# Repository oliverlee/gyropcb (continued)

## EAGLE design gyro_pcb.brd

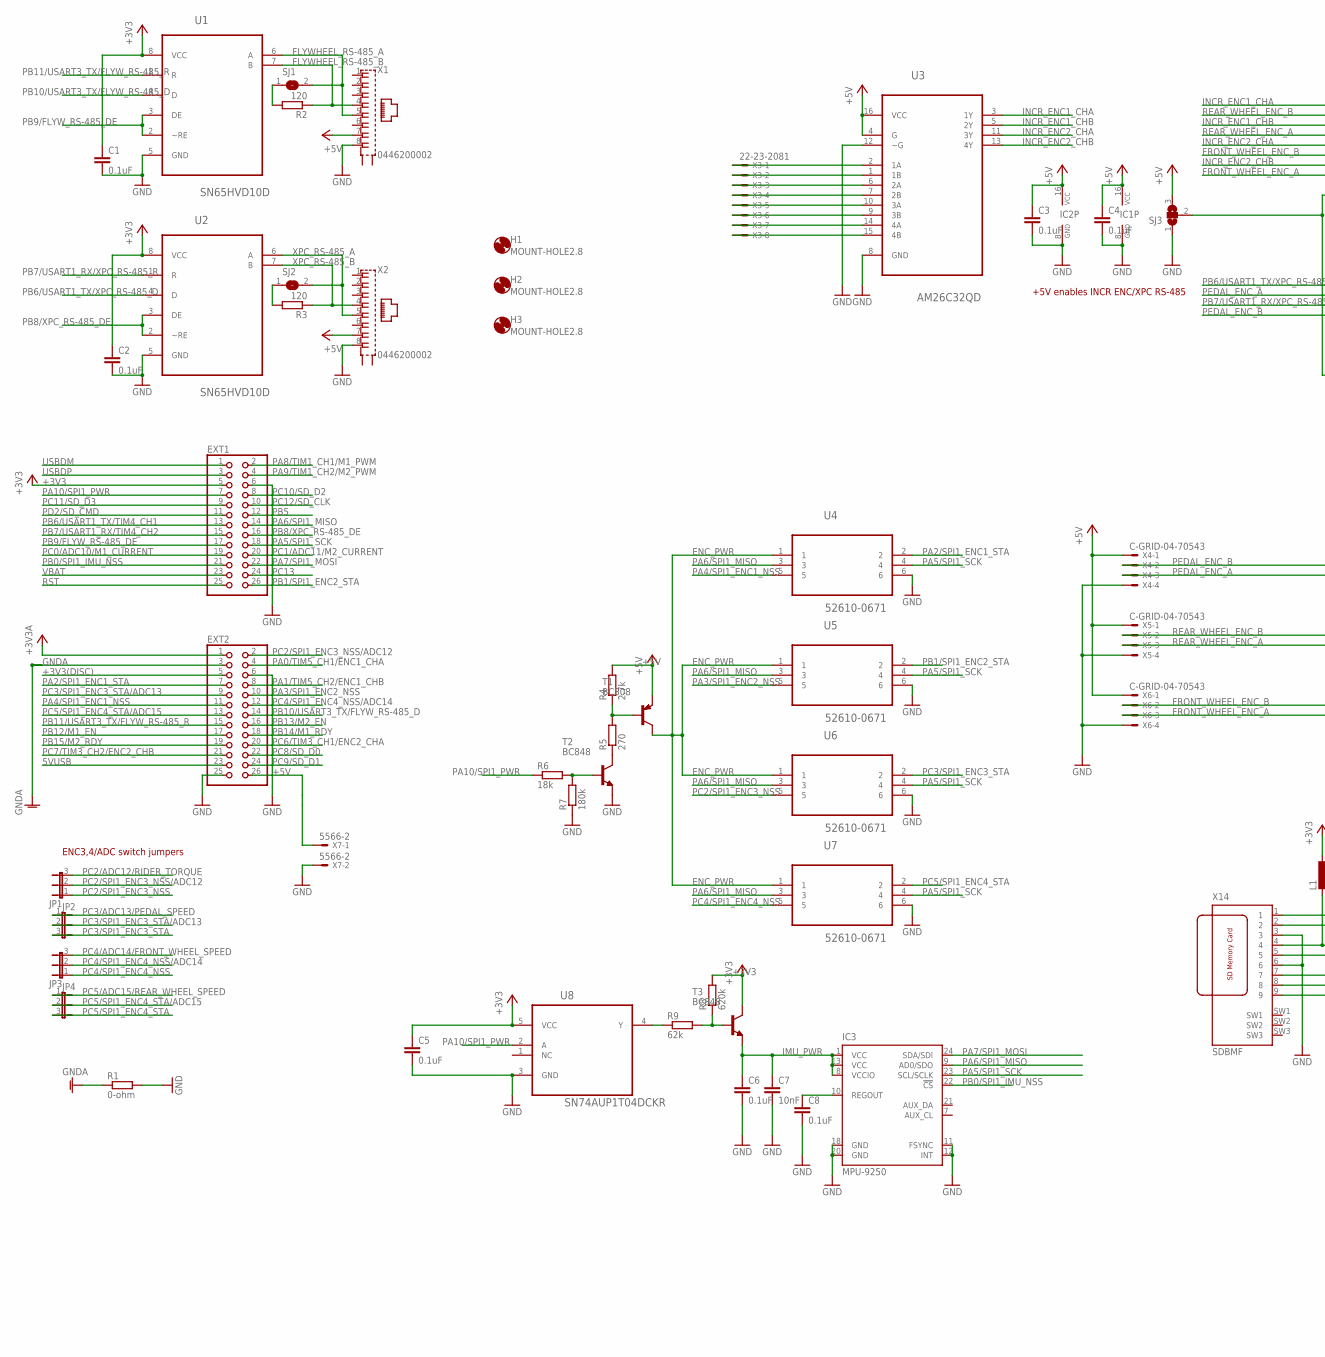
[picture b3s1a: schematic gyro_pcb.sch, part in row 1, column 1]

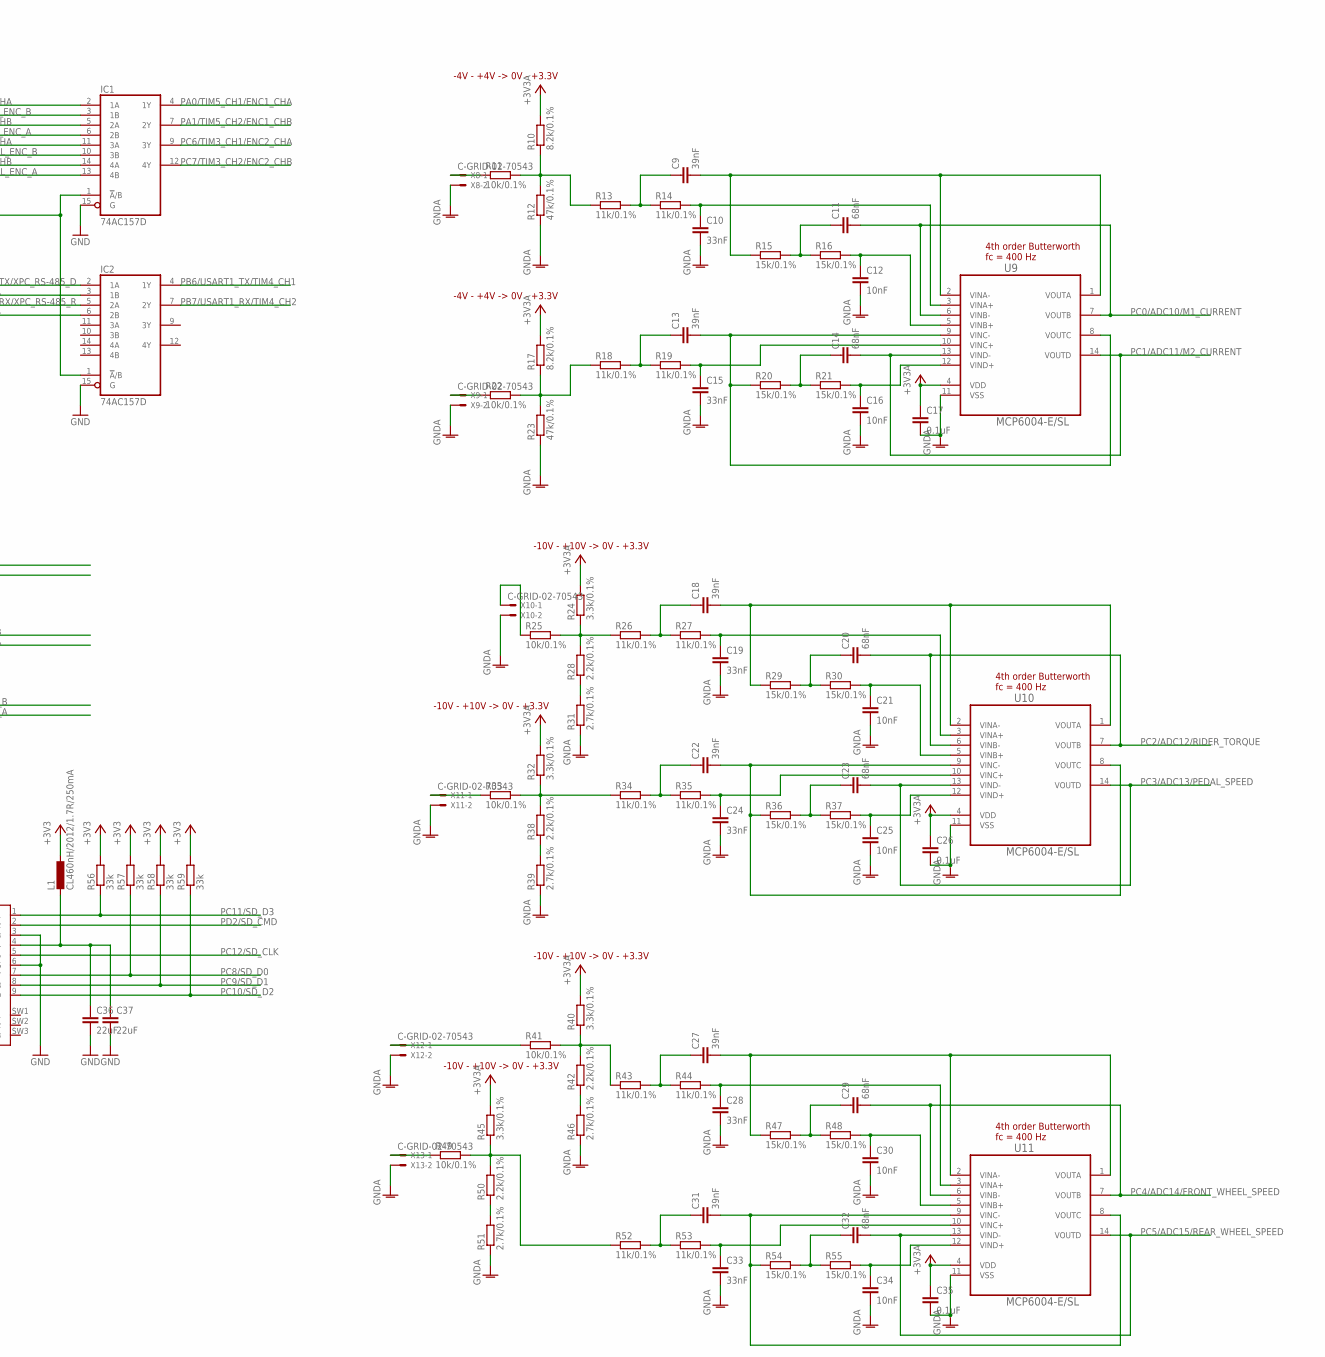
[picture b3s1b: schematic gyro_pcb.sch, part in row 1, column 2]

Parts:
C1, C2, C3, C4, C5, C6, C8, C17, C26, C35: 0.1uF; C0603
C7, C12, C16, C21, C25, C30, C34: 10nF; C0603
C9, C13, C18, C22, C27, C31: 39nF; C0603
C10, C15, C19, C24, C28, C33: 33nF; C0603
C11, C14, C20, C23, C29, C32: 68nF; C0603
C36, C37: 22uF; C0603
EXT1, EXT2: PINHD-2X13; 2X13
H1, H2, H3: MOUNT-HOLE2.8; 2,8
IC1, IC2: 74AC157D; SO16
IC3: MPU-9250; QFN24-SMALL
JP1, JP2, JP3, JP4: JP2E; JP2
L1: CL460nH/2012/1.7R/250mA; L2825P
R1: 0-ohm; R1218
R2, R3: 120; R0603
R4: 2.7k; R1210
R5: 270; R1210
R6: 18k; R0603
R7: 180k; R0603
R8: 620k; R0603
R9: 62k; R0603
R10, R17: 8.2k/0.1%; R0603
R11, R22, R25, R33, R41, R49: 10k/0.1%; R0603
R12, R23: 47k/0.1%; R0603
R13, R14, R18, R19, R26, R27, R34, R35, R43, R44, R52, R53: 11k/0.1%; R0603
R15, R16, R20, R21, R29, R30, R36, R37, R47, R48, R54, R55: 15k/0.1%; R0603
R24, R32, R40, R45: 3.3k/0.1%; R0603
R28, R38, R42, R50: 2.2k/0.1%; R0603
R31, R39, R46, R51: 2.7k/0.1%; R0603
R56, R57, R58, R59: 33k; R0603
SJ1, SJ2: SJ
SJ3: SJ2W; SJ_2
T1: BC808; SOT23-BEC
T2, T3: BC848; SOT23
U1, U2: SN65HVD10D; SOIC127P600X175-8N
U3: AM26C32QD; SOIC127P600X175-16N
U4, U5, U6, U7: 52610-0671; MOLEX_52610-0671
U8: SN74AUP1T04DCKR; SOT65P210X110-5N
U9, U10, U11: MCP6004-E/SL; SOIC127P600X175-14N
X1, X2: 0446200002
X3: 22-23-2081
X4, X5, X6: C-GRID-04-70543; 70543-04
X7: 5566-2
X8, X9, X10, X11, X12, X13: C-GRID-02-70543; 70543-02
X14: SDBMF; SDBMF-009XXBXX2

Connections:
5VUSB: EXT2.23
+3V3: C1.1, C2.1, C5.1, EXT1.5, L1.1, R8.2, R56.2, R57.2, R58.2, R59.2, T3.3 (C), U1.8 (VCC), U2.8 (VCC), U8.5 (VCC)
+3V3(DISC): EXT2.5
+3V3A: C17.1, C26.1, C35.1, EXT2.1, R10.2, R17.2, R24.2, R32.2, R40.2, R45.2, U9.4 (VDD), U10.4 (VDD), U11.4 (VDD)
+5V: C3.1, C4.1, EXT2.26, IC1.16 (VCC), IC2.16 (VCC), R4.2, SJ3.3, T1.E, U3.4 (G), U3.16 (VCC), X1.7, X2.7, X4.1, X5.1, X6.1, X7.1
ENC1_CHA+: U3.1 (1B), X3.2
ENC1_CHA-: U3.2 (1A), X3.1
ENC1_CHB+: U3.7 (2B), X3.4
ENC1_CHB-: U3.6 (2A), X3.3
ENC2_CHA+: U3.9 (3B), X3.6
ENC2_CHA-: U3.10 (3A), X3.5
ENC2_CHB+: U3.15 (4B), X3.8
ENC2_CHB-: U3.14 (4A), X3.7
ENC_PWR: T1.C, U4.1, U5.1, U6.1, U7.1
FLYWHEEL_RS-485_A: SJ1.2, U1.6 (A), X1.5
FLYWHEEL_RS-485_B: R2.1, U1.7 (B), X1.4
FRONT_WHEEL_ENC_A: IC1.13 (4B), X6.3
FRONT_WHEEL_ENC_B: IC1.10 (3B), X6.2
GND: C1.2, C2.2, C3.2, C4.2, C5.2, C6.2, C7.2, C8.2, C36.2, C37.2, EXT1.6, EXT2.6, EXT2.25, IC1.8 (GND), IC1.15 (G), IC2.8 (GND), IC2.15 (G), IC3.11 (FSYNC), IC3.12 (INT), IC3.18 (GND), IC3.20 (GND), R1.2, R7.1, SJ3.1, T2.2 (E), U1.5 (GND), U2.5 (GND), U3.8 (GND), U3.12 (~G), U4.6, U5.6, U6.6, U7.6, U8.3 (GND), X1.8, X2.8, X4.4, X5.4, X6.4, X7.2, X14.3, X14.6
GNDA: C10.2, C12.2, C15.2, C16.2, C17.2, C19.2, C21.2, C24.2, C25.2, C26.2, C28.2, C30.2, C33.2, C34.2, C35.2, EXT2.3, R1.1, R12.1, R23.1, R31.1, R39.1, R46.1, R51.1, U9.11 (VSS), U10.11 (VSS), U11.11 (VSS), X8.2, X9.2, X10.2, X11.2, X12.2, X13.2
IMU_PWR: C6.1, C7.1, IC3.1 (VCC), IC3.8 (VCCIO), IC3.13 (VCC), T3.2 (E)
INCR_ENC1_CHA: IC1.2 (1A), U3.3 (1Y)
INCR_ENC1_CHB: IC1.5 (2A), U3.5 (2Y)
INCR_ENC2_CHA: IC1.11 (3A), U3.11 (3Y)
INCR_ENC2_CHB: IC1.14 (4A), U3.13 (4Y)
unnamed: C8.1, IC3.10 (REGOUT)
unnamed: R8.1, R9.2, T3.1 (B)
unnamed: R4.1, R5.2, T1.B
unnamed: R5.1, T2.3 (C)
unnamed: R6.2, R7.2, T2.1 (B)
unnamed: R28.1, R31.2
unnamed: C18.1, R26.2, R27.1
unnamed: C19.1, R27.2, U10.3 (VINA+)
unnamed: C18.2, R29.1, U10.1 (VOUTA), U10.2 (VINA-)
unnamed: R24.1, R25.2, R26.1, R28.2
unnamed: C22.1, R34.2, R35.1
unnamed: C24.1, R35.2, U10.10 (VINC+)
unnamed: C22.2, R36.1, U10.8 (VOUTC), U10.9 (VINC-)
unnamed: C23.1, R36.2, R37.1
unnamed: R10.1, R11.2, R12.2, R13.1
unnamed: R22.1, X9.1
unnamed: R32.1, R33.2, R34.1, R38.2
unnamed: C25.1, R37.2, U10.12 (VIND+)
unnamed: C36.1, C37.1, L1.2, X14.4
unnamed: R2.2, SJ1.1
unnamed: C9.1, R13.2, R14.1
unnamed: C21.1, R30.2, U10.5 (VINB+)
unnamed: C20.1, R29.2, R30.1
unnamed: R3.2, SJ2.1
unnamed: C27.1, R43.2, R44.1
unnamed: C28.1, R44.2, U11.3 (VINA+)
unnamed: C27.2, R47.1, U11.1 (VOUTA), U11.2 (VINA-)
unnamed: C10.1, R14.2, U9.3 (VINA+)
unnamed: C9.2, R15.1, U9.1 (VOUTA), U9.2 (VINA-)
unnamed: C12.1, R16.2, U9.5 (VINB+)
unnamed: C13.1, R18.2, R19.1
unnamed: C15.1, R19.2, U9.10 (VINC+)
unnamed: C13.2, R20.1, U9.8 (VOUTC), U9.9 (VINC-)
unnamed: C14.1, R20.2, R21.1
unnamed: C16.1, R21.2, U9.12 (VIND+)
unnamed: R9.1, U8.4 (Y)
unnamed: C31.1, R52.2, R53.1
unnamed: C33.1, R53.2, U11.10 (VINC+)
unnamed: C31.2, R54.1, U11.8 (VOUTC), U11.9 (VINC-)
unnamed: C32.1, R54.2, R55.1
unnamed: R49.1, X13.1
unnamed: C34.1, R55.2, U11.12 (VIND+)
unnamed: C30.1, R48.2, U11.5 (VINB+)
unnamed: R17.1, R18.1, R22.2, R23.2
unnamed: C29.1, R47.2, R48.1
unnamed: R41.1, X12.1
unnamed: C11.1, R15.2, R16.1
unnamed: IC1.1 (!A!/B), IC2.1 (!A!/B), SJ3.2
unnamed: R25.1, X10.1
unnamed: R11.1, X8.1
unnamed: R38.1, R39.2
unnamed: R40.1, R41.2, R42.2, R43.1
unnamed: R42.1, R46.2
unnamed: R45.1, R49.2, R50.2, R52.1
unnamed: R50.1, R51.2
unnamed: R33.1, X11.1
PA0/TIM5_CH1/ENC1_CHA: EXT2.4, IC1.4 (1Y)
PA1/TIM5_CH2/ENC1_CHB: EXT2.8, IC1.7 (2Y)
PA2/SPI1_ENC1_STA: EXT2.7, U4.2
PA3/SPI1_ENC2_NSS: EXT2.10, U5.5
PA4/SPI1_ENC1_NSS: EXT2.11, U4.5
PA5/SPI1_SCK: EXT1.18, IC3.23 (SCL/SCLK), U4.4, U5.4, U6.4, U7.4
PA6/SPI1_MISO: EXT1.14, IC3.9 (AD0/SDO), U4.3, U5.3, U6.3, U7.3
PA7/SPI1_MOSI: EXT1.22, IC3.24 (SDA/SDI)
PA8/TIM1_CH1/M1_PWM: EXT1.2
PA9/TIM1_CH2/M2_PWM: EXT1.4
PA10/SPI1_PWR: EXT1.7, R6.1, U8.2 (A)
PB0/SPI1_IMU_NSS: EXT1.21, IC3.22 (!CS)
PB1/SPI1_ENC2_STA: EXT1.26, U5.2
PB5: EXT1.12
PB6/USART1_TX/TIM4_CH1: EXT1.13, IC2.4 (1Y)
PB6/USART1_TX/XPC_RS-485_D: IC2.2 (1A), U2.4 (D)
PB7/USART1_RX/TIM4_CH2: EXT1.15, IC2.7 (2Y)
PB7/USART1_RX/XPC_RS-485_R: IC2.5 (2A), U2.1 (R)
PB8/XPC_RS-485_DE: EXT1.16, U2.2 (~RE), U2.3 (DE)
PB9/FLYW_RS-485_DE: EXT1.17, U1.2 (~RE), U1.3 (DE)
PB10/USART3_TX/FLYW_RS-485_D: EXT2.14, U1.4 (D)
PB11/USART3_TX/FLYW_RS-485_R: EXT2.15, U1.1 (R)
PB12/M1_EN: EXT2.17
PB13/M2_EN: EXT2.16
PB14/M1_RDY: EXT2.18
PB15/M2_RDY: EXT2.19
PC0/ADC10/M1_CURRENT: C11.2, EXT1.19, U9.6 (VINB-), U9.7 (VOUTB)
PC1/ADC11/M2_CURRENT: C14.2, EXT1.20, U9.13 (VIND-), U9.14 (VOUTD)
PC2/ADC12/RIDER_TORQUE: C20.2, JP1.3, U10.6 (VINB-), U10.7 (VOUTB)
PC2/SPI1_ENC3_NSS: JP1.1, U6.5
PC2/SPI1_ENC3_NSS/ADC12: EXT2.2, JP1.2
PC3/ADC13/PEDAL_SPEED: C23.2, JP2.1, U10.13 (VIND-), U10.14 (VOUTD)
PC3/SPI1_ENC3_STA: JP2.3, U6.2
PC3/SPI1_ENC3_STA/ADC13: EXT2.9, JP2.2
PC4/ADC14/FRONT_WHEEL_SPEED: C29.2, JP3.3, U11.6 (VINB-), U11.7 (VOUTB)
PC4/SPI1_ENC4_NSS: JP3.1, U7.5
PC4/SPI1_ENC4_NSS/ADC14: EXT2.12, JP3.2
PC5/ADC15/REAR_WHEEL_SPEED: C32.2, JP4.1, U11.13 (VIND-), U11.14 (VOUTD)
PC5/SPI1_ENC4_STA: JP4.3, U7.2
PC5/SPI1_ENC4_STA/ADC15: EXT2.13, JP4.2
PC6/TIM3_CH1/ENC2_CHA: EXT2.20, IC1.9 (3Y)
PC7/TIM3_CH2/ENC2_CHB: EXT2.21, IC1.12 (4Y)
PC8/SD_D0: EXT2.22, R57.1, X14.7
PC9/SD_D1: EXT2.24, R58.1, X14.8
PC10/SD_D2: EXT1.8, R59.1, X14.9
PC11/SD_D3: EXT1.9, R56.1, X14.1
PC12/SD_CLK: EXT1.10, X14.5
PC13: EXT1.24
PD2/SD_CMD: EXT1.11, X14.2
PEDAL_ENC_A: IC2.3 (1B), X4.3
PEDAL_ENC_B: IC2.6 (2B), X4.2
REAR_WHEEL_ENC_A: IC1.6 (2B), X5.3
REAR_WHEEL_ENC_B: IC1.3 (1B), X5.2
RST: EXT1.25
USBDM: EXT1.1
USBDP: EXT1.3
VBAT: EXT1.23
XPC_RS-485_A: SJ2.2, U2.6 (A), X2.5
XPC_RS-485_B: R3.1, U2.7 (B), X2.4

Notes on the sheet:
-4V - +4V -> 0V - +3.3V
4th order Butterworth fc = 400 Hz
-10V - +10V -> 0V - +3.3V
+5V enables INCR ENC/XPC RS-485
ENC3,4/ADC switch jumpers

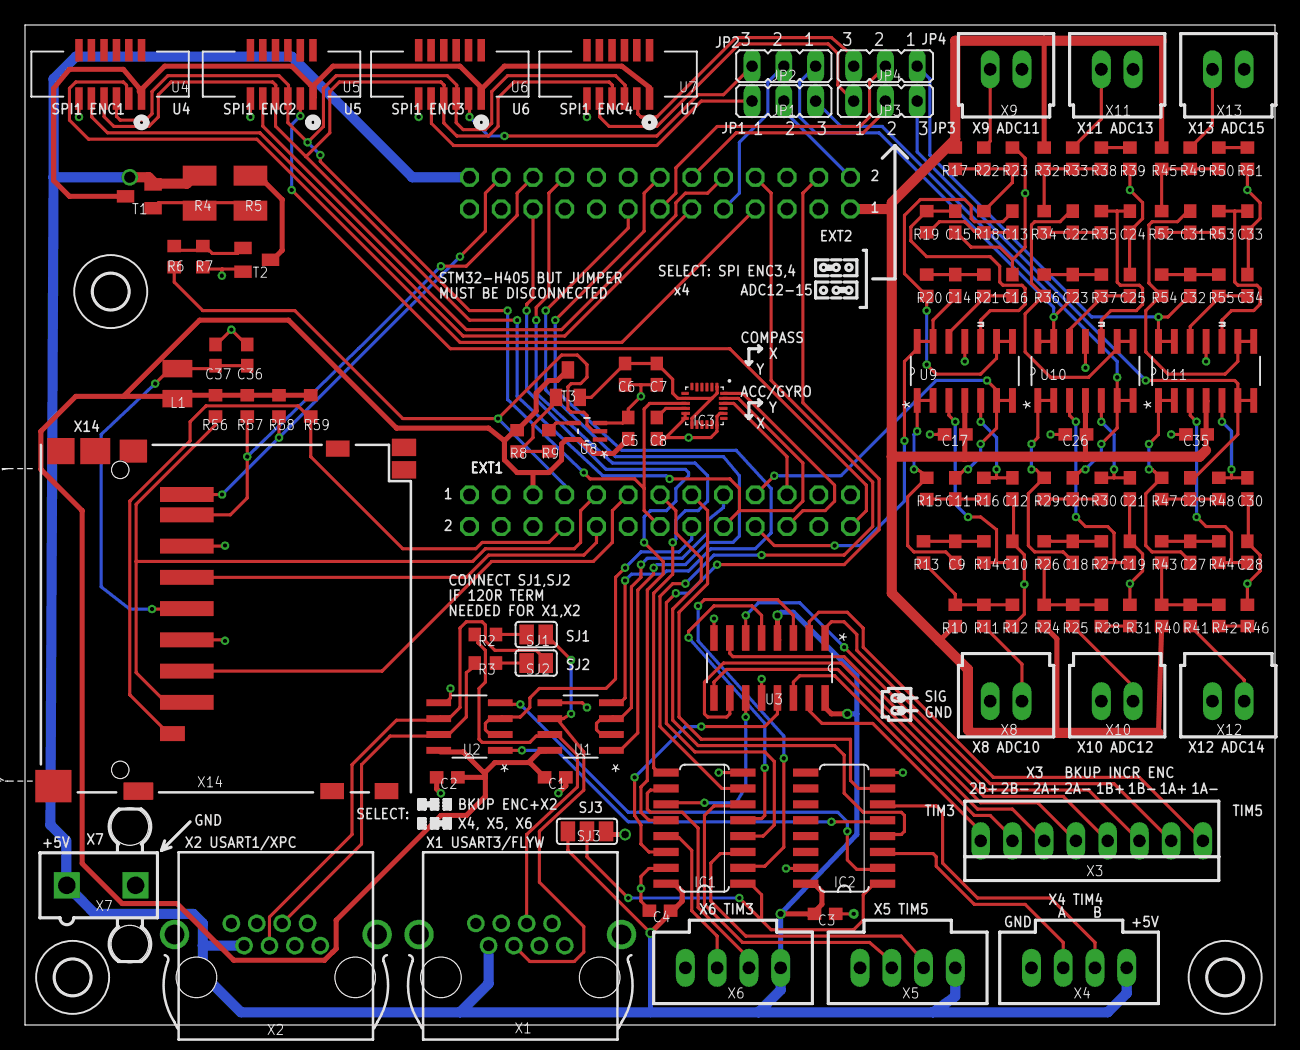
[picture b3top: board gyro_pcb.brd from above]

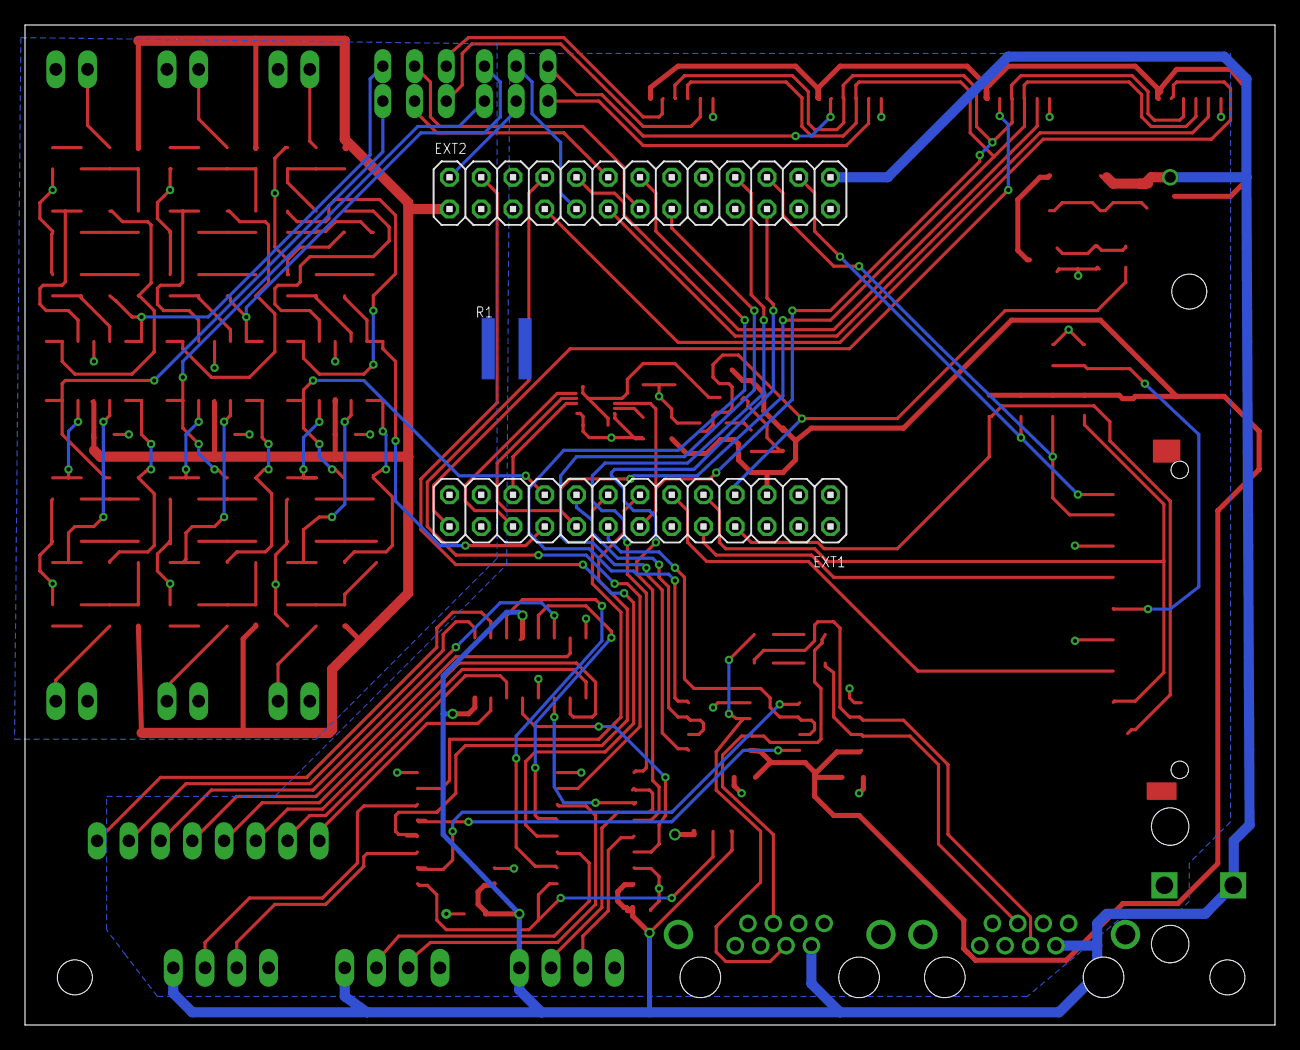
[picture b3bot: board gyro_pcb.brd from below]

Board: 2 copper layers, 100.0 x 80.0 mm, 140 parts (3 on the bottom side), 126 nets.

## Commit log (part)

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2015-12-07 Initial pcb schematic
2015-12-07 Reduce lowpass Butterworth filter cutoff to 400 Hz
2015-12-07 Isolate voltage and ground supplies
    Create isolated analog ground, digital ground, and ground for DC-DC
    converter. Use analog +3.3V supply for analog low pass filters.
2015-12-07 Externally connect GND and GNDA
    Connect digital and analog grounds externally as stated in application
    note AN4488.
2015-12-07 Remove OSX attribute file
2015-12-09 Add RJ-45 connectors for RS-485
    Add RJ-45 connectors for flywheel and xpc target communication via
    RS-485. Connector pin-out follows specification for 2W-MODBUS RJ45.
2015-12-09 Add low-pass Butterworth filter for bike analog signals
    Add low-pass Butterworth filters for steer-by-wire bicycle pedal, front
    wheel, and rear wheel signals.
2015-12-09 Add analog input select jumpers
    Add jumpers to select between additional analog or quadrature encoder
    input.
2015-12-10 Add connector for torque sensor
    Add library for M12U 8-pole receiver for torque sensor connector. Add
    connector to schematic and measurement logic.
2015-12-10 Add jumper to always enable torque sensor measurement
2015-12-10 Fix SPI PWR switch connections
2015-12-10 Add connectors for analog inputs
    Add Molex 22-23-2041 solid header, vertical, with friction lock, 3 pin
    for analog inputs: pedal speed, front wheel speed, and rear wheel speed.
2015-12-10 Add connectors for analog tachometers
    Add connectors for DC motors used as tachometers for sensing pedal
    speed, front wheel speed, rear wheel speed. Voltage range from -10 V to
    +10V to reduced to 0 V to 3.3 V and pass through a 4th order low-pass
    Butterworth filter with cutoff frequency at 400 Hz.
2015-12-10 Add torque sensor signal labels
2015-12-10 Change connectors for analog input tachometers
    Replace with Molex SL headers.
2015-12-10 Add connectors for gear tooth encoders
    Gear tooth encoders use pinouts as specified in the GTS35/GTS45 gear
    tooth sensor datasheet. The PCB cannot be directly connected to the
    sensor as the connector used is a Molex SL header and an AMP 282088-1
    mating connector is required for the sensor cable.
2015-12-11 Add selection mux for bicycle encoder inputs
    Add jumper select between gyro backup encoders and XPC RS-485
    communication or bicycle rear, front, and pedal encoders.
2015-12-11 Add L78L voltage regulator device to component library
    Add +18V, 100 mA L78L positive voltage regulator in SOT-89 package.
    http://www.mouser.com/ds/2/389/CD00000446-355303.pdf
2015-12-11 Add regulated +18V supply to torque sensor
    Provide regulated +18V to torque sensor allowing for +24V or +36V
    batteries.
2015-12-11 Change values on resistors for torque measurement
    Increase resistor values for torque measurement switch.
2015-12-11 Fix incorrect NPN transistor in BJT switches
2015-12-11 Fix ERC errors
2015-12-11 Define new +3.3V supply for analog signals
2015-12-11 Add values to DC-DC converter capacitors
2015-12-11 Remove unnecessary analog select jumpers
2015-12-11 Remove encoder select mux
    The Olimex STM32-H4405 board has enough pins that the encoder mux is not
    necessary.
2015-12-11 Label all microcontroller pins for gyro components
2016-01-19 Create initial board layout
    Resistors and capacitors are grouped by subcircuit and still need to be
    placed correctly.
2016-01-20 Add missing connectors for separate boards
    Add power and differential quadrature encoder connector. Place all
    components in board layout.
2016-01-20 Add AGND plane
2016-01-20 Add ground plane, power traces
    Add ground plane, traces for +5V and +3V3A.
2016-01-20 Autoroute board components
2016-01-20 Add +3V3A, +3V3, and +5V power traces
2016-01-20 Draw IMU wires
2016-01-20 Fit RJ-49 components on board
2016-01-20 Redraw +3V3 power trace
2016-01-22 Set board layout and routing
2016-01-22 Complete selectors for encoder/ADC input
    Complete labels for quad-mux ICs to select gimbal backup incremental
    encoders + XPC RS-485 or separate incremental encoder inputs. Add
    jumpers to receive ADC input over SPI ENC3,4.
2016-01-22 Add ADC select jumpers to board layout
2016-01-22 Complete routing of board components
2016-01-25 Fixup trace/pad connections and add vias to ground
    Move traces to touch pad corners. Add vias to ground for small ground
    traces. Increase clearance for connectors.
2016-01-25 Add bypass capacitors
2016-01-27 Renumber board components
2016-01-27 Add ADC jumper usage to silkscreen layer
2016-01-28 Mirror Olimex STM32-H405 on board layout
    Mirror Olimex on board so that pins are correctly defined for attaching
    board from top.
2016-01-28 Manually route board traces
    Define GND, GNDA planes. Define +5V, +3V3, +3V3A power traces. Begin
    route board components.
2016-01-28 Swap pins used for ENC2 and IMU NSS
    Swap pins PA3, PB0 to PA3/SPI1_ENC2_NSS, PB0/SPI1_IMU_NSS to reduce
    trace length.
2016-01-28 Route IMU SPI pins
2016-01-28 Swap pins PA2, PA10
    Swap pins PA2, PA10 to PA2/SPI1_ENC1_STA, PA10/SPI1_PWR.
2016-01-28 Route all digital signals
2016-01-28 Rename +3V3 pin on EXT2
    Rename pin to +3V3(DISC) and disconnect from +3V3 power supply to clear
    autorouting problems.
2016-01-28 Fix silkscreen labels for STM32-H405 EXT
    Fix silkscreen labels for Olimex STM32-H405 EXT1 and EXT2. Label pins 1
    and 2 for each EXT.
2016-01-28 Place names of all components
    Place names of all components. This layer will not be included in the
    silkscreen layer due to the large amount of resistors and capacitors.
2016-01-29 Add silkscreen layer
    Add silkscreen layer with labels for connectors. Add descriptions for
    jumpers. Show coordinate axes for IMU.
2016-01-29 Move connector X3 and silkscreen labels
    Move connector X3 to allow pinout labels for connector X4.
2016-01-29 Rename microcontroller schematic and board
2016-01-29 Rename power board schematic
2016-01-30 Add voltage input range for ADCs on silkscreen
2016-01-30 Remove components on microcontroller board
2016-01-30 Roughly place power board components
2016-02-01 Place and route components
2016-02-02 Add connectors for +24V input and +5V output
2016-02-02 Add jumper to disable +18V output regulator
2016-02-02 Add torque sensor connector
2016-02-02 Add mount holes
2016-02-03 Add silkscreen layer
2016-02-03 Add torque measurement enable connector
2016-02-03 Change torque measurement connector name
    Change torque measurement connector name to X15 to match microcontroller
    pcb.
2016-02-03 Add ADC and INCR ENC pins definitions to silkscreeen
2016-02-04 Add board and hole position dimensions
2016-02-04 Add board and hole position dimensions
    Add board mount hole position dimensions. Change dimension units from
    mil to mm.
2016-02-15 Add ground planes on top layer
2016-02-15 Add +24V power plane to top layer
2016-03-17 Merge GND and GNDA planes
    The analog signals are converted to 12-bit values and do not require a
    separate ground plane.
2016-03-17 Copy +24V power trace and set clearance
    Copy +24V power track to bottom layer and set clearance to 12 mil
    (~0.3 mm).
2016-03-17 Fix DRC clearance issues
2016-03-17 Open soldermask for +24V top power trace
    Draw tStop and tCream layers on +24 top power trace to increase current
    capacity.
2016-03-18 Change +24V connectors
    Change to holes and solder 6 AWG wires to board.
2016-03-18 Add bypass capacitors
    Add missing bypass capacitors for buck circuit in power board and U3 in
    mc board.
2016-03-18 Replace RS-485 half-duplex transceivers
    Use RS-485 full-duplex instead of half-duplex transceivers. Add STM32F4
    application note on ADC usage.
2016-03-18 Change connector X15
    Change torque sensor measurement signal to active low and remove +3V3.
2016-03-18 Replace Butterworth low pass filters
    Replace with 2-pole passive RC filters. Add solder switches to set
    cutoff frequency to 200 or 400 Hz.
2016-03-19 Replace SPI encoders with SSI encoders
    Replace SPI encoders with RLS RMB20SC (SSI) 13-bit encoders in
    schematic. Add necessary ICs to use on SPI1 bus.
2016-03-19 Add missing motor signal connector
    Add missing connector for PWM, EN, RDY signals for motors M1, M2. Use
    the same connector for SSI encoders and motor signals.
2016-03-23 Finish component layout and routing
    Redo layout and routing after replacing RS-485 ICs, SSI encoders, analog
    filters.
2016-03-23 Add motor connector to power board
2016-03-23 Change M12U 8POLE pad shape to round
    Change pad shape of M12U 8POLE package from square to round. Update
    component in power board.
2016-03-23 Renumber parts in mc schematic
2016-03-23 Renumber components in power board to match mc board
    Renumber jacks such that signals that connect the mc and power boards
    share the same name. Renumber other components.
2016-03-23 Finish silkscreen layer for mc board
2016-03-23 Add SO-8 package for L78L
    Add SO-8 package for L78L voltage regulator as SOT-89 package is not
    available on digikey.
2016-03-23 Fix values and packages for inductors and capacitors
    mc_pcb:
    Fix package size for L1 to 0805 (2012 metric) and value to 470 nH. Add
    additional value information for MPU9250 capacitors (C3, C4, C6).
    power_pcb:
    Change package of U2 to SO8. Fix values for C2, C3.
2016-03-23 Add TI and Molex libraries
2016-03-23 Add SH50C inductor to component library
2016-03-23 Fix buck converter inductor, capacitors
    Add SparkFun capacitor library containing PANASONIC_H13 package. In buck
    converter, fix package for C1, C2, L1 and rearrange traces.
2016-03-23 Connect MPU-9250 INT pin to STM32F4
2016-03-23 Fix reversed connector pinouts in power board
    Fix pinout for motor drive and connectors J6, J7.
2016-03-23 Change connector for J5, J10, J11, J12
    Use Molex C-Grid 5 position connector for torque sensor J5. Reverse pins
    for analog connectors J10, J11, J12.
2016-03-24 Finish place and route of power board
2016-03-24 Add chamfers to right angles in mc board
2016-03-24 Remove datasheets for unused components
2016-03-25 Add Amphenol SD/MMC component to library
2016-03-25 Replace X1 with Amphenol micro SD socket
2016-03-25 Add name to micro SD card package
2016-03-29 Add second IMU
    Add second MPU-9250 on schematic and layout. Second IMU is not directly
    connected to the microcontroller but must be connected via provided
    pinhead.
2016-03-29 Add silkscreen for IMU2
2016-03-29 Fix unconnected grounds
2016-03-29 Route airwaves in power board
2016-03-29 Fix spacing of a few traces
2016-03-29 Replace MPU-9250 component
    Add library for MPU-9250 component and replace in schematic.
2016-03-29 Reduce MPU-9250 pad size
    Reduce MPU-9250 pad width from 0.25 mm to 0.23 mm to meet DRC.
2016-03-29 Fix drill distance to satisfy DRC
2016-03-30 Replace ISO35 with ISO30
    Replace ISO35 3.3V RS-485 transceiver with ISI3086 5V transceiver.
2016-03-30 Add ISO3080 datasheet
2016-03-30 Add bypass capacitors for ISO30 VCC2
2016-04-01 Add Molex Milli-Grid THT connectors
2016-04-01 Replace FPC connectors and route traces
2016-06-10 Fix incorrect label for GPIOB_PIN11
2016-06-10 Add README with BOM and errata
    Add README with link to bill of materials and errata section.
2016-06-16 Note incorrect S4 description
2016-07-05 Add note on disconnected +24V, GND mount pads
2016-09-30 Fix Kistler torque measurement line
    The Kistler torque sensor signal output line will only be valid if the
    measurement line pulled low after the sensor is powered on. The previous
    configuration with Q2 would not pull the measurement line to ground. As
    Q2 has been removed, the line name has changed from 'TORQUE_MEAS_NEN' to
    'TORQUE_MEAS_EN'.
2016-10-03 Note problems with Kistler measure line
2016-10-13 Update README.md
    Silkscreen wrong for motor connectors
2016-10-18 Note incorrect S2 description
2016-10-21 Update README.md
    Hall sensor for motor 2 has missing trace
2016-10-21 Note missing pullup resistor for SDIO CMD
2016-10-21 Add microcontroller and motor drive models to README
2017-03-02 Add missing Invensense MPU-9250 datasheet
2017-03-02 Readme update
